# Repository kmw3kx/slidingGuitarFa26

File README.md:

# slidingGuitarFa26
Repo for all of the electronics &amp; code for my Fa26 capstone group 

## Daisy Pins

## Basic idea

6 string guitar with glass slider attached to linear actuator.

From gemini:

$$\text{Total Encoder Positions} = \frac{575\text{ mm}}{0.1894\text{ mm/count}} \approx \mathbf{3,036\text{ discrete positions}}$$

My original idea was to use pitchbend midi control for slider position, but it doesn't appear to be completely necessary. But it will fit for now.

Then I will use a cc channel or 2 for the gains on the Op-amps

I will build this demo in puredata so that I can start composing for it.

## Work Log

### 11-1-26 
-Bob: I was able to work on the pcb designs for the guitar. Still need to do the power supply board, but want to wait until we further define what parts we'll use for that (especially since I've already built a prototype for it). 

Here's the amplifier board. Should be able to be mounted near the output coils:

Here's the vactrol/optoisolator board. This is designed to be placed directly under the strings so that the exposed LED's will show which strings are being played automatically:

I've designed a 3D-printed structure for the vactrols. I'm thinking that a single part will be printed to hold all 6 LSR's and LED's in place, with a case to fully cover the LED's (besides just a lil peep hole). While these parts might be able to be held by the soldered lsr, they really should be screw-mounted. 

Here's the daisy board; note that the design isn't completely done: 

Some notes about the boards:
-Not all traces have been fully added; these are designed to be put on stripboard. I have been experimenting with using a small desktop CNC to etch pcb traces, but I've been fairly unsuccessful due to the copper delaminating. I'm hoping that stripboard will allow the boards to be easier to fabricate; any breaks to be cut have been noted on the user.1/3 layers: etching & drilling respectively. I've been using Carbide Create/Motion to generate and run the gcode for the CNC
-I want to use 3D printing, pin header and sockets, and standard dupont connectors for these boards, since they are what is most readily available. My idea is that small 3D-printed sleeves can go around each dupont in a single structure that can be screwed to the mount under the board. Need to design this to communicate the idea better. More screwholes may need to be added to make mounting more repairable.
-Need to clarify what exactly is being soldered into each space. For example, the motor signal holes will likely just have dupont wires soldered to the board, and then the above idea will be on the H-bridge board.
-I'm thinking that the silkscreen will be able to be put on the stripboard using a CO2 laser for etching. Maybe etch onto painters tape, and then spray paint for actual white text (DIY technique I've seen online).

### 11-4-26
-Bob: I've been working on terminations/connectors for the wiring,  & ensuring the last daisy seed3 doesn't get fried by the motor driver (RIP). Also building up the courage to get back to working on that. 

Dupont connectors are so ubiquitous, it makes sense to use them and just make 3D printed cases to keep them connected. But I'm not sure if connecting them as butt joints, or turning them into vga cables is best:

I've gone ahead and laid out the boards in a practical arrangement to fit onto the body of the guitar. I'm hoping this graphic will be suitable for the team to start working on laying out where everything goes, and how everything will be wired up. I wish I could find a way to better render these boards individually into step files, but laying them out in KiCAD is suitable for now.

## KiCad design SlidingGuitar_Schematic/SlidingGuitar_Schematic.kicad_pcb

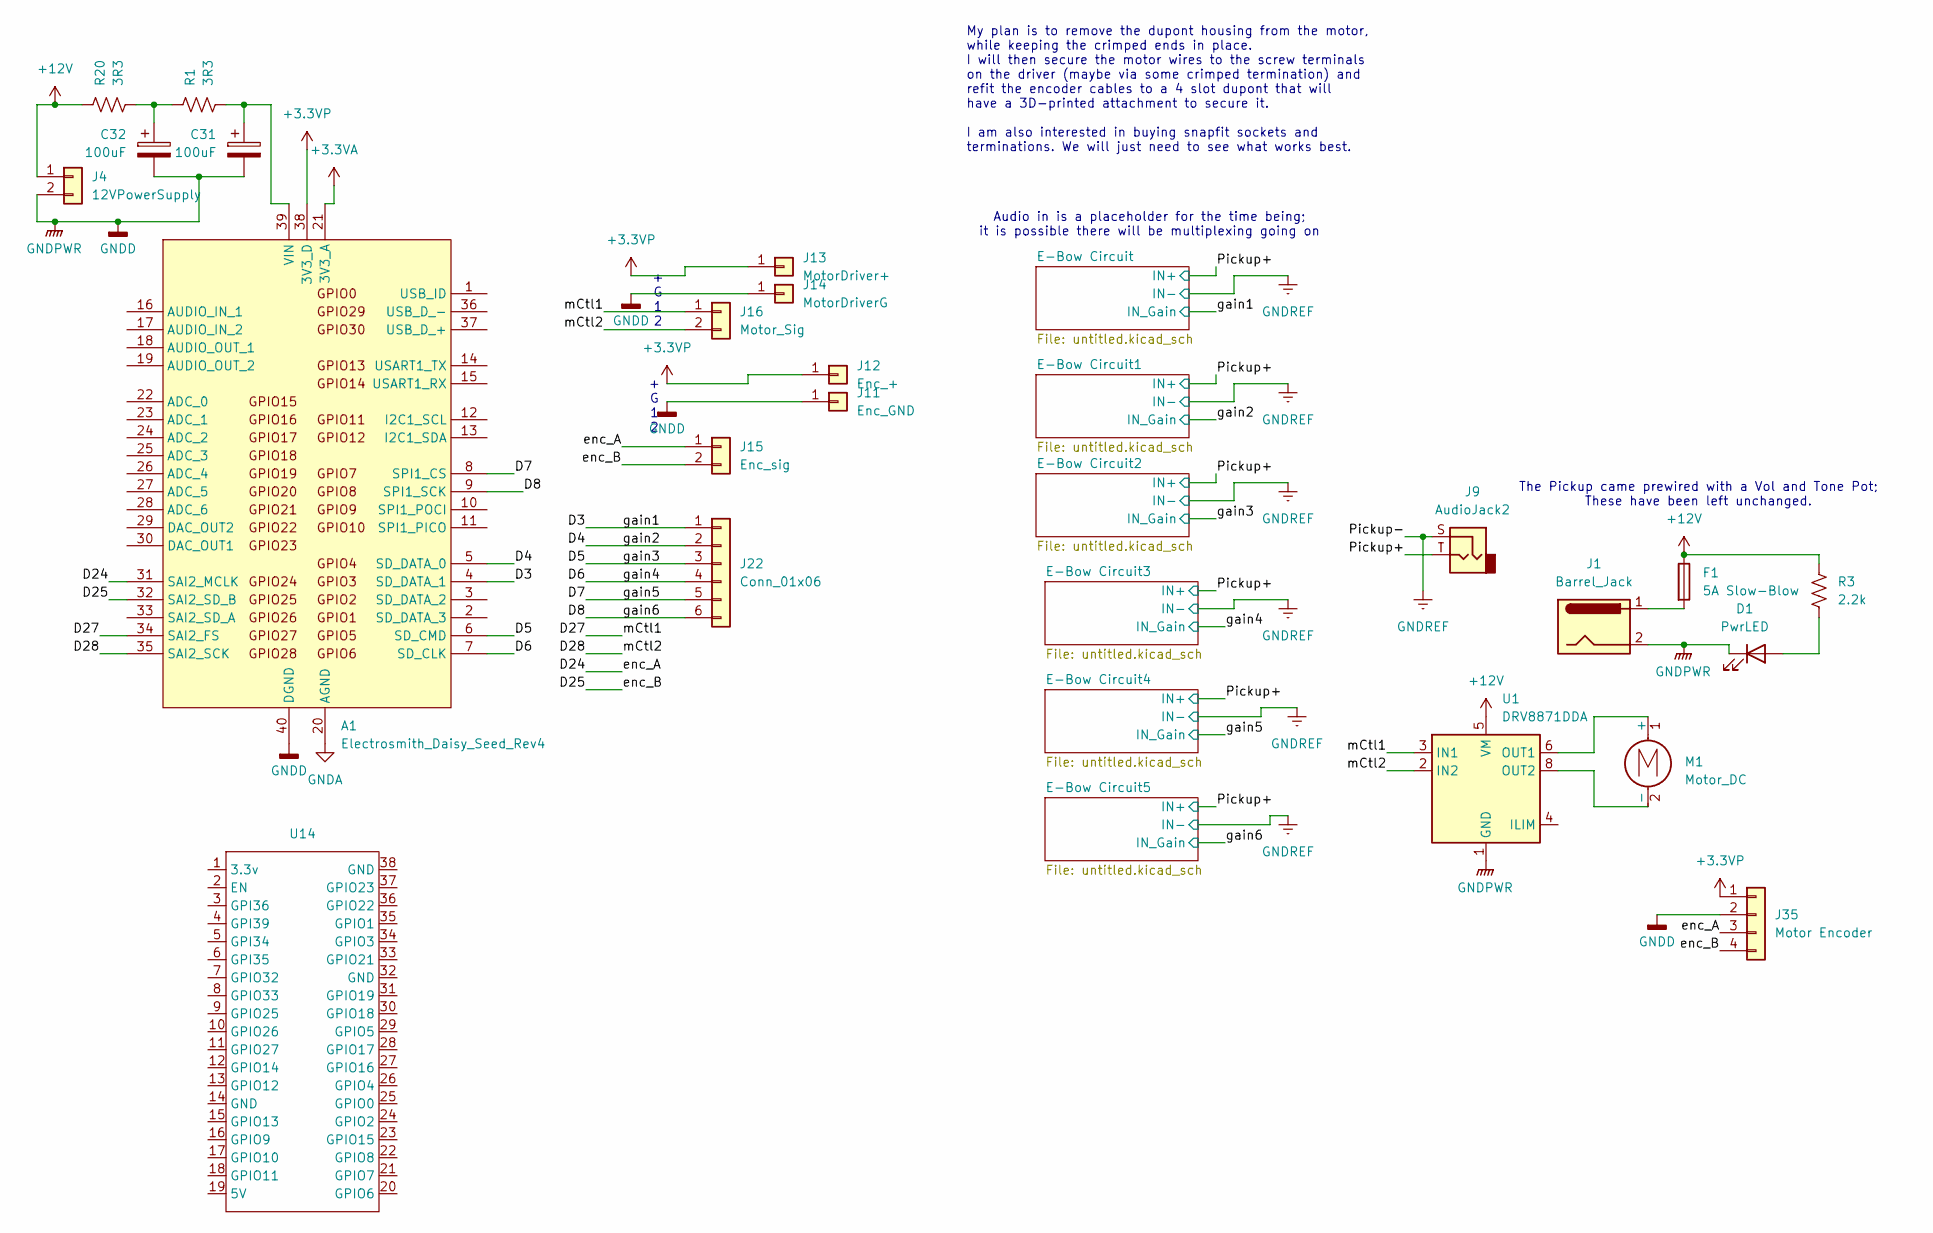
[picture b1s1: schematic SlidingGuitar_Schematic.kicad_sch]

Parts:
A1: Electrosmith_Daisy_Seed_Rev4; Electrosmith_Daisy_Seed
C31, C32: 100uF; CP_Radial_D8.0mm_P5.00mm
D1: PwrLED
F1: 5A Slow-Blow
J1: Barrel_Jack; BarrelJack_Horizontal
J4: 12VPowerSupply; PinHeader_1x02_P2.54mm_Vertical
J9: AudioJack2
J11: Enc_GND; PinHeader_1x01_P2.54mm_Vertical
J12: Enc_+; PinHeader_1x01_P2.54mm_Vertical
J13: MotorDriver+; PinHeader_1x01_P2.54mm_Vertical
J14: MotorDriverG; PinHeader_1x01_P2.54mm_Vertical
J15: Enc_sig; PinHeader_1x02_P2.54mm_Vertical
J16: Motor_Sig; PinHeader_1x02_P2.54mm_Vertical
J22: Conn_01x06; PinHeader_1x06_P2.54mm_Vertical
J35: Motor Encoder
M1: Motor_DC
R1, R20: 3R3; R_Axial_DIN0207_L6.3mm_D2.5mm_P7.62mm_Horizontal
R3: 2.2k
U1: DRV8871DDA; Texas_HTSOP-8-1EP_3.9x4.9mm_P1.27mm_EP2.95x4.9mm_Mask2.4x3.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
U14: PinSocket_2x19_P2.54mm_Vertical

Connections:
+3.3VA: A1.21 (3V3_A)
+3.3VP: A1.38 (3V3_D), J12.1 (Pin_1_1), J13.1 (Pin_1_1), J35.1
+12V: F1.1, J4.1, R3.1, R20.1, U1.5 (VM); also elsewhere on the board
/D3: A1.4 (SD_DATA_1), J22.1; also elsewhere on the board
/D4: A1.5 (SD_DATA_0), J22.2; also elsewhere on the board
/D5: A1.6 (SD_CMD), J22.3; also elsewhere on the board
/D6: A1.7 (SD_CLK), J22.4; also elsewhere on the board
/D7: A1.8 (SPI1_CS), J22.5; also elsewhere on the board
/D8: A1.9 (SPI1_SCK), J22.6; also elsewhere on the board
/D24: A1.31 (SAI2_MCLK), J15.1, J35.3
/D25: A1.32 (SAI2_SD_B), J15.2, J35.4
/D27: A1.34 (SAI2_FS), J16.1, U1.3 (IN1)
/D28: A1.35 (SAI2_SCK), J16.2, U1.2 (IN2)
GNDA: A1.20 (AGND)
GNDD: A1.40 (DGND), C31.2, C32.2, D1.1 (K), J1.2, J4.2, J11.1 (Pin_1_1), J14.1 (Pin_1_1), J35.2, U1.1 (GND), U1.7 (GND), U1.9 (GND); also elsewhere on the board
unnamed: A1.39 (VIN), C31.1, R1.2
unnamed: C32.1, R1.1, R20.2
unnamed: D1.2 (A), R3.2
unnamed: F1.2, J1.1
unnamed: M1.1 (+), U1.6 (OUT1)
unnamed: M1.2 (-), U1.8 (OUT2)

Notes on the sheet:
The Pickup came prewired with a Vol and Tone Pot; These have been left unchanged.
+ G 1 2
Audio in is a placeholder for the time being; it is possible there will be multiplexing going on
My plan is to remove the dupont housing from the motor, while keeping the crimped ends in place. I will then secure the motor wires to the screw terminals on the driver (maybe via some crimped termination) and refit the encoder cables to a 4 slot dupont that will have a 3D-printed attachment to sec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

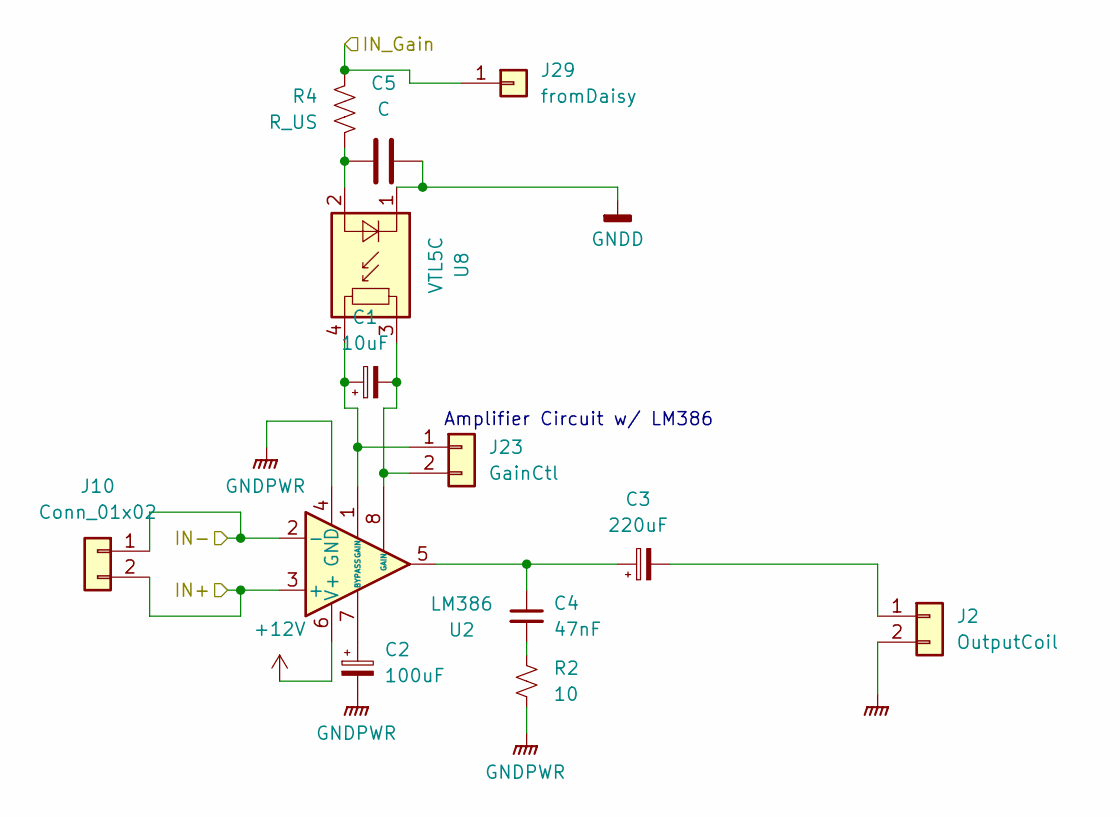
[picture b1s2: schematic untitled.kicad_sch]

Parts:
C1: 10uF; CP_Radial_D5.0mm_P2.50mm
C2: 100uF; CP_Radial_D8.0mm_P5.00mm
C3: 220uF; CP_Radial_D8.0mm_P5.00mm
C4: 47nF; C_Disc_D3.8mm_W2.6mm_P2.50mm
C5: C; PinSocket_1x02_P2.54mm_Vertical
J2: OutputCoil; PinHeader_1x02_P2.54mm_Vertical
J10: Conn_01x02; PinHeader_1x02_P2.54mm_Vertical
J23: GainCtl; PinHeader_1x02_P2.54mm_Vertical
J29: fromDaisy; PinHeader_1x01_P2.54mm_Horizontal
R2: 10; R_Axial_DIN0204_L3.6mm_D1.6mm_P5.08mm_Horizontal
R4: R_US; R_Axial_DIN0207_L6.3mm_D2.5mm_P7.62mm_Horizontal
U2: LM386; DIP-8_W7.62mm
U8: VTL5C; PerkinElmer_VTL5C

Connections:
+12V: U2.6 (V+); also elsewhere on the board
/D3: J29.1 (Pin_1_1), R4.1; also elsewhere on the board
/Pickup+: J10.2, U2.3 (+); also elsewhere on the board
GNDD: C2.2, C5.2, J2.2, R2.2, U2.4 (GND), U8.1 (-); also elsewhere on the board
GNDREF: J10.1, U2.2 (-); also elsewhere on the board
unnamed: C3.1, C4.1, U2.5
unnamed: C4.2, R2.1
unnamed: C3.2, J2.1
unnamed: C1.1, J23.1, U2.1 (GAIN), U8.4
unnamed: C1.2, J23.2, U2.8 (GAIN), U8.3
unnamed: C2.1, U2.7 (BYPASS)
unnamed: C5.1, R4.2, U8.2 (+)

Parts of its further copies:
C6, C11, C16, C21, C26: 100uF; CP_Radial_D8.0mm_P5.00mm
C7, C12, C17, C22, C27: C; PinSocket_1x02_P2.54mm_Vertical
C8, C13, C18, C23, C28: 10uF; CP_Radial_D5.0mm_P2.50mm
C9, C14, C19, C24, C29: 47nF; C_Disc_D3.8mm_W2.6mm_P2.50mm
C10, C15, C20, C25, C30: 220uF; CP_Radial_D8.0mm_P5.00mm
J3, J5, J6, J7, J8: OutputCoil; PinHeader_1x02_P2.54mm_Vertical
J17, J18, J19, J20, J21: Conn_01x02; PinHeader_1x02_P2.54mm_Vertical
J24, J25, J26, J27, J28: GainCtl; PinHeader_1x02_P2.54mm_Vertical
J30, J31, J32, J33, J34: fromDaisy; PinHeader_1x01_P2.54mm_Horizontal
R6, R9, R12, R15, R18: R_US; R_Axial_DIN0207_L6.3mm_D2.5mm_P7.62mm_Horizontal
R7, R10, R13, R16, R19: 10; R_Axial_DIN0204_L3.6mm_D1.6mm_P5.08mm_Horizontal
U3, U4, U5, U6, U7: LM386; DIP-8_W7.62mm
U9, U10, U11, U12, U13: VTL5C; PerkinElmer_VTL5C

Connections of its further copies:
+12V: U3.6 (V+), U4.6 (V+), U5.6 (V+), U6.6 (V+), U7.6 (V+); also elsewhere on the board
/D4: J30.1 (Pin_1_1), R6.1; also elsewhere on the board
/D5: J31.1 (Pin_1_1), R9.1; also elsewhere on the board
/D6: J32.1 (Pin_1_1), R12.1; also elsewhere on the board
/D7: J33.1 (Pin_1_1), R15.1; also elsewhere on the board
/D8: J34.1 (Pin_1_1), R18.1; also elsewhere on the board
/Pickup+: J17.2, J18.2, J19.2, J20.2, J21.2, U3.3 (+), U4.3 (+), U5.3 (+), U6.3 (+), U7.3 (+); also elsewhere on the board
GNDD: C6.2, C7.2, C11.2, C12.2, C16.2, C17.2, C21.2, C22.2, C26.2, C27.2, J3.2, J5.2, J6.2, J7.2, J8.2, R7.2, R10.2, R13.2, R16.2, R19.2, U3.4 (GND), U4.4 (GND), U5.4 (GND), U6.4 (GND), U7.4 (GND), U9.1 (-), U10.1 (-), U11.1 (-), U12.1 (-), U13.1 (-); also elsewhere on the board
GNDREF: J17.1, J18.1, J19.1, J20.1, J21.1, U3.2 (-), U4.2 (-), U5.2 (-), U6.2 (-), U7.2 (-); also elsewhere on the board
unnamed: C9.2, R7.1
unnamed: C9.1, C10.1, U3.5
unnamed: C14.1, C15.1, U4.5
unnamed: C14.2, R10.1
unnamed: C19.1, C20.1, U5.5
unnamed: C19.2, R13.1
unnamed: C24.1, C25.1, U6.5
unnamed: C24.2, R16.1
unnamed: C29.1, C30.1, U7.5
unnamed: C29.2, R19.1
unnamed: C10.2, J3.1
unnamed: C15.2, J5.1
unnamed: C20.2, J6.1
unnamed: C25.2, J7.1
unnamed: C30.2, J8.1
unnamed: C8.1, J24.1, U3.1 (GAIN), U9.4
unnamed: C8.2, J24.2, U3.8 (GAIN), U9.3
unnamed: C13.1, J25.1, U4.1 (GAIN), U10.4
unnamed: C13.2, J25.2, U4.8 (GAIN), U10.3
unnamed: C18.1, J26.1, U5.1 (GAIN), U11.4
unnamed: C18.2, J26.2, U5.8 (GAIN), U11.3
unnamed: C23.1, J27.1, U6.1 (GAIN), U12.4
unnamed: C23.2, J27.2, U6.8 (GAIN), U12.3
unnamed: C28.1, J28.1, U7.1 (GAIN), U13.4
unnamed: C28.2, J28.2, U7.8 (GAIN), U13.3
unnamed: C6.1, U3.7 (BYPASS)
unnamed: C11.1, U4.7 (BYPASS)
unnamed: C16.1, U5.7 (BYPASS)
unnamed: C21.1, U6.7 (BYPASS)
unnamed: C26.1, U7.7 (BYPASS)
unnamed: C7.1, R6.2, U9.2 (+)
unnamed: C12.1, R9.2, U10.2 (+)
unnamed: C17.1, R12.2, U11.2 (+)
unnamed: C22.1, R15.2, U12.2 (+)
unnamed: C27.1, R18.2, U13.2 (+)

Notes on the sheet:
Amplifier Circuit w/ LM386

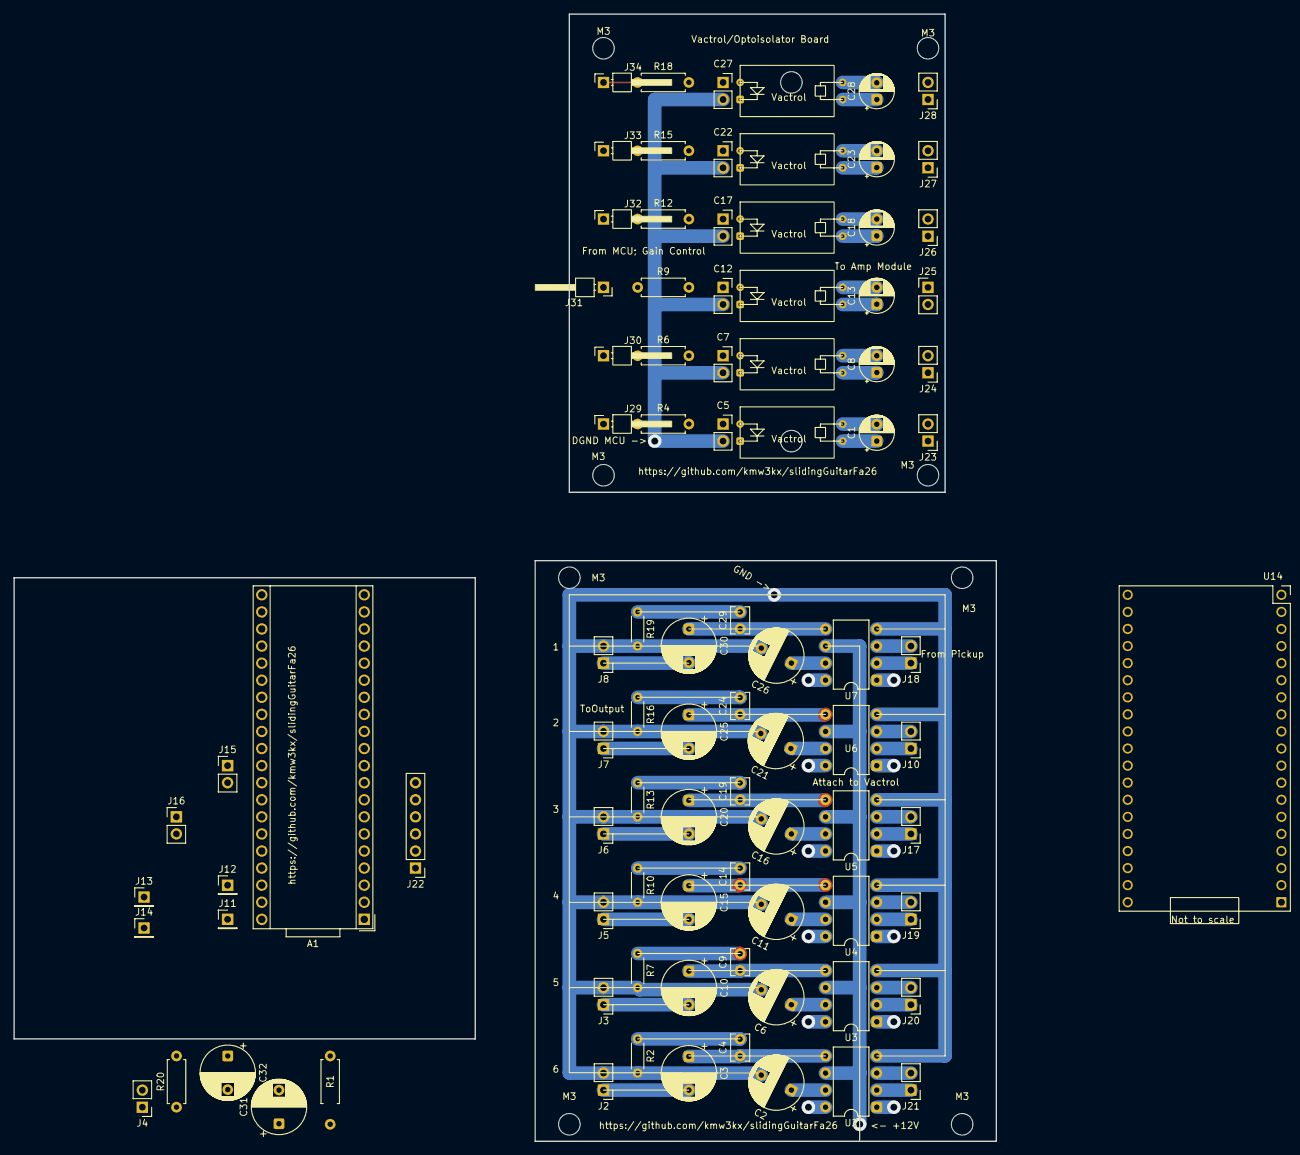
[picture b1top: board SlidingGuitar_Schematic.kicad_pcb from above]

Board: 2 copper layers, 146.1 x 167.6 mm, 100 parts (0 on the bottom side), 59 nets.

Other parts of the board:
M3, M3#2, M3#3, M3#4, M3#5, M3#6, M3#7, M3#8: MountingHole_3.2mm_M3
